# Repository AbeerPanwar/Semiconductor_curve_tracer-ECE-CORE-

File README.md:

# Semiconductor_curve_tracer-ECE-CORE-

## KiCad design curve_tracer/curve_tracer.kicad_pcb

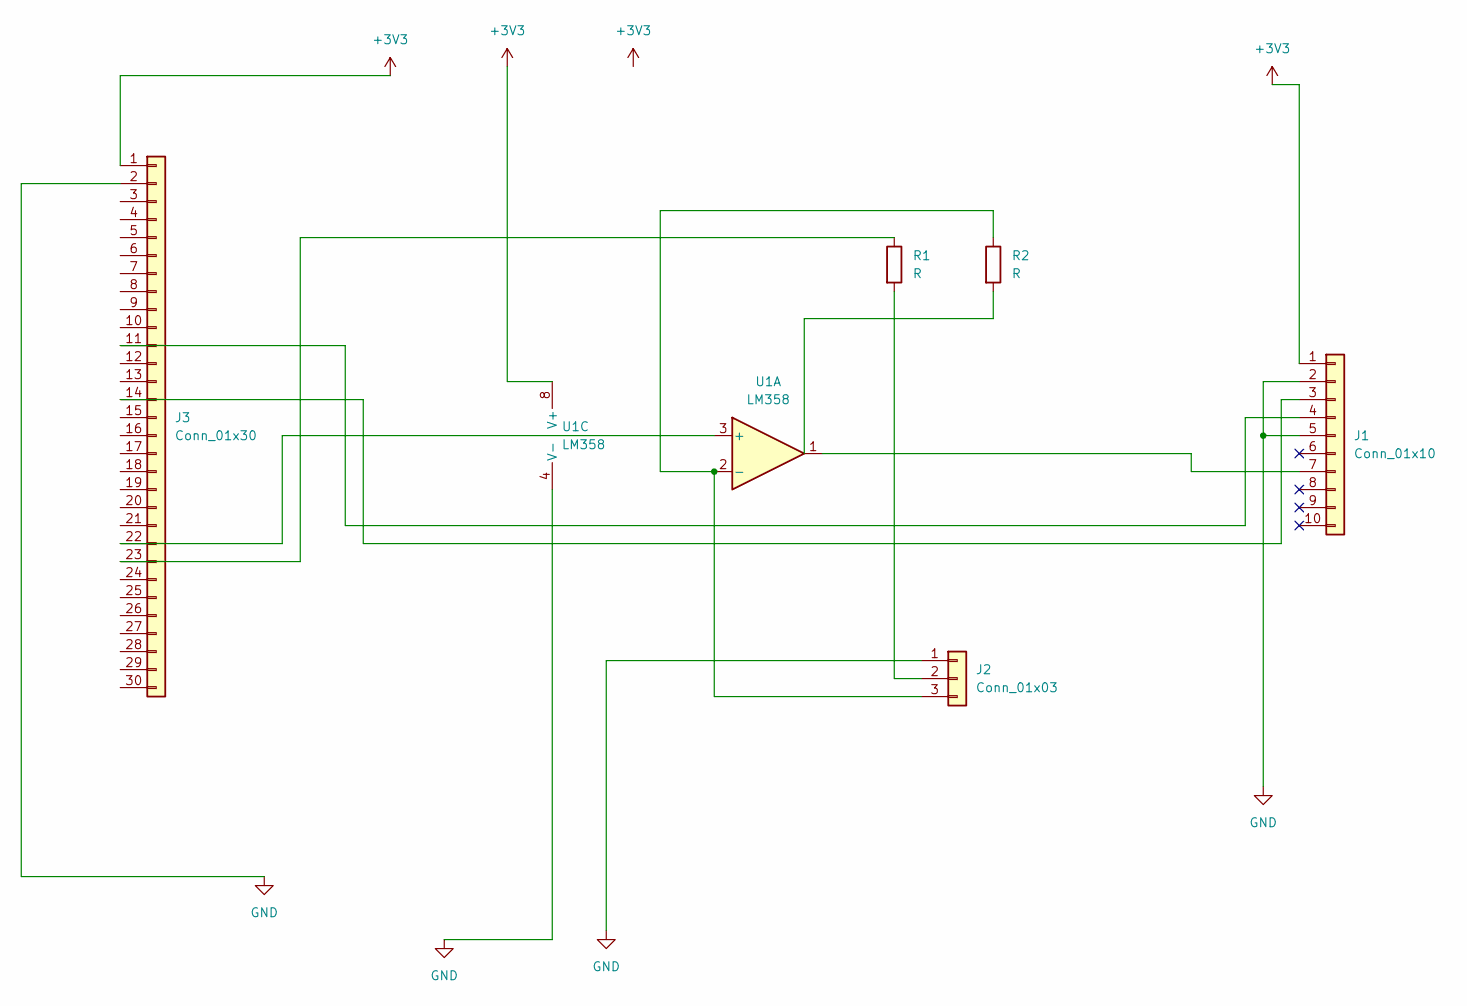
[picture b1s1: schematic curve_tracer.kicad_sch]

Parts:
J1: Conn_01x10; PinHeader_1x10_P2.54mm_Vertical
J2: Conn_01x03; PinHeader_1x03_P2.54mm_Vertical
J3: Conn_01x30; PinHeader_1x30_P2.54mm_Vertical
R1, R2: R; R_Axial_DIN0207_L6.3mm_D2.5mm_P10.16mm_Horizontal
U1: LM358; DIP-8_W7.62mm

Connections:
+3V3: J1.1, J3.1, U1.8 (V+)
GND: J1.2, J1.5, J2.1, J3.2, U1.4 (V-)
unnamed: J1.3, J3.14
unnamed: J1.4, J3.11
unnamed: J1.7, U1.1
unnamed: J2.2, R1.2
unnamed: J2.3, R2.1, U1.2 (-)
unnamed: J3.22, U1.3 (+)
unnamed: J3.23, R1.1

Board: 2 copper layers, 6 parts (0 on the bottom side), 9 nets, no tracks yet.

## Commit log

2026-04-21 Iniial commit
2026-05-16 modified cpp code with the new feat of Iot using wifi to communicate with flutter app
2026-05-16 fixed flutter code and refactured it
2026-05-17 final updates
2026-05-17 final changes
2026-05-17 fix an issue
